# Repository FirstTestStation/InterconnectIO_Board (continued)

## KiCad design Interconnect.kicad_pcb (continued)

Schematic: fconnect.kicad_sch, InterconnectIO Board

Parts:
J1, J2: 9001-11961C00A; 900111961C00A; Manufacturer_Part_Number 9001-11961C00A
J3, J4: 7760; Manufacturer_Part_Number 7760; Mouser_Part_Number 534-7760
NT48: JA1; NetTie-2_Front1.0mm
NT49: JB18; NetTie-2_Front1.0mm
NT50: K10_H; NetTie-2_Front1.0mm
NT51: K31_L; NetTie-2_Front1.0mm
NT52: JA2; NetTie-2_Front1.0mm
NT53: JB19; NetTie-2_Front1.0mm
NT54: K10_L; NetTie-2_Front1.0mm
NT55: K34_H; NetTie-2_Front1.0mm
NT56: JA3; NetTie-2_Front1.0mm
NT57: JB20; NetTie-2_Front1.0mm
NT58: K13_H; NetTie-2_Front1.0mm
NT59: K34_L; NetTie-2_Front1.0mm
NT60: JA4; NetTie-2_Front1.0mm
NT61: JB21; NetTie-2_Front1.0mm
NT62: K13_L; NetTie-2_Front1.0mm
NT63: K37_H; NetTie-2_Front1.0mm
NT64: JA5; NetTie-2_Front1.0mm
NT65: JB22; NetTie-2_Front1.0mm
NT66: K16_H; NetTie-2_Front1.0mm
NT67: K37_L; NetTie-2_Front1.0mm
NT68: JA6; NetTie-2_Front1.0mm
NT69: JB23; NetTie-2_Front1.0mm
NT70: K16_L; NetTie-2_Front1.0mm
NT71: JA7; NetTie-2_Front1.0mm
NT72: JB24; NetTie-2_Front1.0mm
NT73: OCH1_H; NetTie-2_Front1.0mm
NT74: JA8; NetTie-2_Front1.0mm
NT75: JB25; NetTie-2_Front1.0mm
NT76: OCH1_L; NetTie-2_Front1.0mm
NT77: K41_H; NetTie-2_Front1.0mm
NT78: JA9; NetTie-2_Front1.0mm
NT79: JB26; NetTie-2_Front1.0mm
NT80: K20_H; NetTie-2_Front1.0mm
NT81: K41_L; NetTie-2_Front1.0mm
NT82: JA10; NetTie-2_Front1.0mm
NT83: JB27; NetTie-2_Front1.0mm
NT84: K20_L; NetTie-2_Front1.0mm
NT85: K44_H; NetTie-2_Front1.0mm
NT86: JA11; NetTie-2_Front1.0mm
NT87: JB28; NetTie-2_Front1.0mm
NT88: K23_H; NetTie-2_Front1.0mm
NT89: K44_L; NetTie-2_Front1.0mm
NT90: JA12; NetTie-2_Front1.0mm
NT91: JB29; NetTie-2_Front1.0mm
NT92: K23_L; NetTie-2_Front1.0mm
NT93: K47_H; NetTie-2_Front1.0mm
NT94: JA13; NetTie-2_Front1.0mm
NT95: JB30; NetTie-2_Front1.0mm
NT96: K26_H; NetTie-2_Front1.0mm
NT97: K47_L; NetTie-2_Front1.0mm
NT98: JA14; NetTie-2_Front1.0mm
NT99: JB31; NetTie-2_Front1.0mm
NT100: K26_L; NetTie-2_Front1.0mm
NT101: VM_I; NetTie-2_Front1.0mm
NT102: JA15; NetTie-2_Front1.0mm
NT103: JB32; NetTie-2_Front1.0mm
NT104: OCH2_H; NetTie-2_Front1.0mm
NT105: VM_T; NetTie-2_Front1.0mm
NT106: JA16; NetTie-2_Front1.0mm
NT107: JC1; NetTie-2_Front1.0mm
NT108: OCH2_L; NetTie-2_Front1.0mm
NT109: K12_H; NetTie-2_Front1.0mm
NT110: JA17; NetTie-2_Front1.0mm
NT111: JC2; NetTie-2_Front1.0mm
NT112: K30_H; NetTie-2_Front1.0mm
NT113: K12_L; NetTie-2_Front1.0mm
NT114: JA18; NetTie-2_Front1.0mm
NT115: JC3; NetTie-2_Front1.0mm
NT116: K30_L; NetTie-2_Front1.0mm
NT117: K15_H; NetTie-2_Front1.0mm
NT118: JA19; NetTie-2_Front1.0mm
NT119: JC4; NetTie-2_Front1.0mm
NT120: K33_H; NetTie-2_Front1.0mm
NT121: K15_L; NetTie-2_Front1.0mm
NT122: JA20; NetTie-2_Front1.0mm
NT123: JC5; NetTie-2_Front1.0mm
NT124: K33_L; NetTie-2_Front1.0mm
NT125: K1_CH; NetTie-2_Front1.0mm
NT126: JA21; NetTie-2_Front1.0mm
NT127: JC6; NetTie-2_Front1.0mm
NT128: K36_H; NetTie-2_Front1.0mm
NT129: K1_CL; NetTie-2_Front1.0mm
NT130: JA22; NetTie-2_Front1.0mm
NT131: JC7; NetTie-2_Front1.0mm
NT132: K36_L; NetTie-2_Front1.0mm
NT133: JA23; NetTie-2_Front1.0mm
NT134: JC8; NetTie-2_Front1.0mm
NT135: SG1_H; NetTie-2_Front1.0mm
NT136: K_OC1; NetTie-2_Front1.0mm
NT137: JA24; NetTie-2_Front1.0mm
NT138: JC9; NetTie-2_Front1.0mm
NT139: SG1_L; NetTie-2_Front1.0mm
NT140: K22_H; NetTie-2_Front1.0mm
NT141: JA25; NetTie-2_Front1.0mm
NT142: JC10; NetTie-2_Front1.0mm
NT143: K40_H; NetTie-2_Front1.0mm
NT144: K22_L; NetTie-2_Front1.0mm
NT145: JA26; NetTie-2_Front1.0mm
NT146: JC11; NetTie-2_Front1.0mm
NT147: K40_L; NetTie-2_Front1.0mm
NT148: K25_H; NetTie-2_Front1.0mm
NT149: JA27; NetTie-2_Front1.0mm
NT150: JC12; NetTie-2_Front1.0mm
NT151: K43_H; NetTie-2_Front1.0mm
NT152: K25_L; NetTie-2_Front1.0mm
NT153: RXH; NetTie-2_Front1.0mm
NT154: JC13; NetTie-2_Front1.0mm
NT155: K43_L; NetTie-2_Front1.0mm
NT156: K2_CH; NetTie-2_Front1.0mm
NT157: RXL; NetTie-2_Front1.0mm
NT158: JC14; NetTie-2_Front1.0mm
NT159: K46_H; NetTie-2_Front1.0mm
NT160: K2_CL; NetTie-2_Front1.0mm
NT161: JA30; NetTie-2_Front1.0mm
NT162: JC15; NetTie-2_Front1.0mm
NT163: K46_L; NetTie-2_Front1.0mm
NT164: TXH; NetTie-2_Front1.0mm
NT165: JC16; NetTie-2_Front1.0mm
NT166: VM_H; NetTie-2_Front1.0mm
NT167: K_OC2; NetTie-2_Front1.0mm
NT168: TXL; NetTie-2_Front1.0mm
NT169: JC17; NetTie-2_Front1.0mm
NT170: VM_L; NetTie-2_Front1.0mm
NT171: K32_H; NetTie-2_Front1.0mm
NT172: JB1; NetTie-2_Front1.0mm
NT173: JC18; NetTie-2_Front1.0mm
NT174: K11_H; NetTie-2_Front1.0mm
NT175: K32_L; NetTie-2_Front1.0mm
NT176: JB2; NetTie-2_Front1.0mm
NT177: JC19; NetTie-2_Front1.0mm
NT178: K11_L; NetTie-2_Front1.0mm
NT179: K35_H; NetTie-2_Front1.0mm
NT180: JB3; NetTie-2_Front1.0mm
NT181: JC20; NetTie-2_Front1.0mm
NT182: K14_H; NetTie-2_Front1.0mm
NT183: K35_L; NetTie-2_Front1.0mm
NT184: JB4; NetTie-2_Front1.0mm
NT185: JC21; NetTie-2_Front1.0mm
NT186: K14_L; NetTie-2_Front1.0mm
NT187: K3_CH; NetTie-2_Front1.0mm
NT188: JB5; NetTie-2_Front1.0mm
NT189: JC22; NetTie-2_Front1.0mm
NT190: K17_H; NetTie-2_Front1.0mm
NT191: K3_CL; NetTie-2_Front1.0mm
NT192: JB6; NetTie-2_Front1.0mm
NT193: JC23; NetTie-2_Front1.0mm
NT194: K17_L; NetTie-2_Front1.0mm
NT195: JB7; NetTie-2_Front1.0mm
NT196: JC24; NetTie-2_Front1.0mm
NT197: KI1_H; NetTie-2_Front1.0mm
NT198: K_OC3; NetTie-2_Front1.0mm
NT199: JB8; NetTie-2_Front1.0mm
NT200: JC25; NetTie-2_Front1.0mm
NT201: KI1_L; NetTie-2_Front1.0mm
NT202: K42_H; NetTie-2_Front1.0mm
NT203: JB9; NetTie-2_Front1.0mm
NT204: JC26; NetTie-2_Front1.0mm
NT205: K21_H; NetTie-2_Front1.0mm
NT206: K42_L; NetTie-2_Front1.0mm
NT207: JB10; NetTie-2_Front1.0mm
NT208: JC27; NetTie-2_Front1.0mm
NT209: K21_L; NetTie-2_Front1.0mm
NT210: K45_H; NetTie-2_Front1.0mm
NT211: JB11; NetTie-2_Front1.0mm
NT212: JC28; NetTie-2_Front1.0mm
NT213: K24_H; NetTie-2_Front1.0mm
NT214: K45_L; NetTie-2_Front1.0mm
NT215: JB12; NetTie-2_Front1.0mm
NT216: JC29; NetTie-2_Front1.0mm
NT217: K24_L; NetTie-2_Front1.0mm
NT218: K4_CH; NetTie-2_Front1.0mm
NT219: JB13; NetTie-2_Front1.0mm
NT220: JC30; NetTie-2_Front1.0mm
NT221: K27_H; NetTie-2_Front1.0mm
NT222: K4_CL; NetTie-2_Front1.0mm
NT223: JB14; NetTie-2_Front1.0mm
NT224: JC31; NetTie-2_Front1.0mm
NT225: K27_L; NetTie-2_Front1.0mm
NT226: VMS_H; NetTie-2_Front1.0mm
NT227: JB15; NetTie-2_Front1.0mm
NT228: JC32; NetTie-2_Front1.0mm
NT229: VMS_L; NetTie-2_Front1.0mm
NT230: JB16; NetTie-2_Front1.0mm
NT231: JB17; NetTie-2_Front1.0mm
NT232: K31_H; NetTie-2_Front1.0mm
TP17: J_A5; Pin_D0.9mm_L10.0mm_W2.4mm_FlatFork
TP18: J_A6; Pin_D0.9mm_L10.0mm_W2.4mm_FlatFork
TP19: K_B23; Pin_D0.9mm_L10.0mm_W2.4mm_FlatFork
TP20: K_B24; Pin_D0.9mm_L10.0mm_W2.4mm_FlatFork
TP21: J_A10; Pin_D0.9mm_L10.0mm_W2.4mm_FlatFork
TP22: J_A23; Pin_D0.9mm_L10.0mm_W2.4mm_FlatFork
TP23: J_B6; Pin_D0.9mm_L10.0mm_W2.4mm_FlatFork
TP24: K_B15; Pin_D0.9mm_L10.0mm_W2.4mm_FlatFork
TP25: K_B16; Pin_D0.9mm_L10.0mm_W2.4mm_FlatFork

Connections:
1W_DATA: NT177.1; also elsewhere on the board
AWG_H: NT135.2; also elsewhere on the board
AWG_L: NT139.2; also elsewhere on the board
B1_COM_H: NT125.1; also elsewhere on the board
B1_COM_L: NT129.1; also elsewhere on the board
B2_COM_H: NT156.1; also elsewhere on the board
B2_COM_L: NT160.1; also elsewhere on the board
B3_COM_H: NT187.1; also elsewhere on the board
B3_COM_L: NT191.1; also elsewhere on the board
B4_COM_H: NT218.1; also elsewhere on the board
B4_COM_L: NT222.1; also elsewhere on the board
B10_H: NT50.2; also elsewhere on the board
B10_L: NT54.2; also elsewhere on the board
B11_H: NT174.2; also elsewhere on the board
B11_L: NT178.2; also elsewhere on the board
B12_H: NT109.2; also elsewhere on the board
B12_L: NT113.2; also elsewhere on the board
B13_H: NT58.2; also elsewhere on the board
B13_L: NT62.2; also elsewhere on the board
B14_H: NT182.2; also elsewhere on the board
B14_L: NT186.2; also elsewhere on the board
B15_H: NT117.2; also elsewhere on the board
B15_L: NT121.2; also elsewhere on the board
B16_H: NT66.2; also elsewhere on the board
B16_L: NT70.2; also elsewhere on the board
B17_H: NT190.2; also elsewhere on the board
B17_L: NT194.2; also elsewhere on the board
B20_H: NT80.2; also elsewhere on the board
B20_L: NT84.2; also elsewhere on the board
B21_H: NT205.2; also elsewhere on the board
B21_L: NT209.2; also elsewhere on the board
B22_H: NT140.2; also elsewhere on the board
B22_L: NT144.2; also elsewhere on the board
B23_H: NT88.2; also elsewhere on the board
B23_L: NT92.2; also elsewhere on the board
B24_H: NT213.2; also elsewhere on the board
B24_L: NT217.2; also elsewhere on the board
B25_H: NT148.2; also elsewhere on the board
B25_L: NT152.2; also elsewhere on the board
B26_H: NT96.2; also elsewhere on the board
B26_L: NT100.2; also elsewhere on the board
B27_H: NT221.2; also elsewhere on the board
B27_L: NT225.2; also elsewhere on the board
B30_H: NT112.2; also elsewhere on the board
B30_L: NT116.2; also elsewhere on the board
B31_H: NT232.2; also elsewhere on the board
B31_L: NT51.2; also elsewhere on the board
B32_H: NT171.2; also elsewhere on the board
B32_L: NT175.2; also elsewhere on the board
B33_H: NT120.2; also elsewhere on the board
B33_L: NT124.2; also elsewhere on the board
B34_H: NT55.2; also elsewhere on the board
B34_L: NT59.2; also elsewhere on the board
B35_H: NT179.2; also elsewhere on the board
B35_L: NT183.2; also elsewhere on the board
B36_H: NT128.2; also elsewhere on the board
B36_L: NT132.2; also elsewhere on the board
B37_H: NT63.2; also elsewhere on the board
B37_L: NT67.2; also elsewhere on the board
B40_H: NT143.2; also elsewhere on the board
B40_L: NT147.2; also elsewhere on the board
B41_H: NT77.2; also elsewhere on the board
B41_L: NT81.2; also elsewhere on the board
B42_H: NT202.2; also elsewhere on the board
B42_L: NT206.2; also elsewhere on the board
B43_H: NT151.2; also elsewhere on the board
B43_L: NT155.2; also elsewhere on the board
B44_H: NT85.2; also elsewhere on the board
B44_L: NT89.2; also elsewhere on the board
B45_H: NT210.2; also elsewhere on the board
B45_L: NT214.2; also elsewhere on the board
B46_H: NT159.2; also elsewhere on the board
B46_L: NT163.2; also elsewhere on the board
B47_H: NT93.2; also elsewhere on the board
B47_L: NT97.2; also elsewhere on the board
CMOD_1: NT107.1; also elsewhere on the board
CMOD_2: NT111.1; also elsewhere on the board
CMOD_3: NT115.1; also elsewhere on the board
CMOD_4: NT119.1; also elsewhere on the board
CUR_SENS_H: NT185.1; also elsewhere on the board
CUR_SENS_L: NT189.1; also elsewhere on the board
DAC_VOUT: NT184.1; also elsewhere on the board
DIG_PWR_IN: NT208.1; also elsewhere on the board
DVM_H: NT166.2; also elsewhere on the board
DVM_I: NT101.2; also elsewhere on the board
DVM_L: NT170.2; also elsewhere on the board
DVM_SENSE_H: NT226.2; also elsewhere on the board
DVM_SENSE_L: NT229.2; also elsewhere on the board
DVM_TRIG: NT105.2; also elsewhere on the board
ETH_RX+: NT153.1; also elsewhere on the board
ETH_RX-: NT157.1; also elsewhere on the board
ETH_TX+: NT164.1; also elsewhere on the board
ETH_TX-: NT168.1; also elsewhere on the board
Earth: J1.MH1, J1.MH2, J2.MH1, J2.MH2, J3.1, J3.2, J3.3, J3.4, J4.1, J4.2, J4.3, J4.4; also elsewhere on the board
GND: J2.C7, J2.C15, J2.C23, NT98.1, NT161.1, NT180.1, NT181.1, NT188.1; also elsewhere on the board
I2C_SCL: NT94.1; also elsewhere on the board
I2C_SDA: NT90.1; also elsewhere on the board
INST_H: NT197.1; also elsewhere on the board
INST_L: NT201.1; also elsewhere on the board
JTAG_IGND: NT122.1; also elsewhere on the board
JTAG_OGND: NT110.1; also elsewhere on the board
JTAG_TCK: NT126.1; also elsewhere on the board
JTAG_TDI: NT118.1; also elsewhere on the board
JTAG_TDO: NT106.1; also elsewhere on the board
JTAG_TGND: NT130.1; also elsewhere on the board
JTAG_TMS: NT114.1; also elsewhere on the board
JTAG_TRST: NT102.1; also elsewhere on the board
K1_LP_C1: NT195.1; also elsewhere on the board
K1_LP_C2: NT131.1; also elsewhere on the board
K1_LP_NC1: NT203.1; also elsewhere on the board
K1_LP_NC2: NT138.1; also elsewhere on the board
K1_LP_NO1: NT199.1; also elsewhere on the board
K1_LP_NO2: NT134.1; also elsewhere on the board
K2_LP_C1: NT207.1; also elsewhere on the board
K2_LP_C2: NT142.1; also elsewhere on the board
K2_LP_NC1: NT215.1; also elsewhere on the board
K2_LP_NC2: NT150.1; also elsewhere on the board
K2_LP_NO1: NT211.1; also elsewhere on the board
K2_LP_NO2: NT146.1; also elsewhere on the board
K3_HP_C1: NT154.1; also elsewhere on the board
K3_HP_C2: NT158.1; also elsewhere on the board
K3_HP_NO1: NT162.1; also elsewhere on the board
K3_HP_NO2: NT165.1; also elsewhere on the board
unnamed: J1.A1, NT48.2
unnamed: J1.A2, NT52.2
unnamed: J1.A3, NT56.2
unnamed: J1.A4, NT60.2
unnamed: J1.A5, NT64.2
unnamed: J1.A6, NT68.2
unnamed: J1.A7, NT71.2
unnamed: J1.A8, NT74.2
unnamed: J1.A9, NT78.2
unnamed: J1.A10, NT82.2
unnamed: J1.A11, NT86.2
unnamed: J1.A12, NT90.2
unnamed: J1.A13, NT94.2
unnamed: J1.A14, NT98.2
unnamed: J1.A15, NT102.2
unnamed: J1.A16, NT106.2
unnamed: J1.A17, NT110.2
unnamed: J1.A18, NT114.2
unnamed: J1.A19, NT118.2
unnamed: J1.A20, NT122.2
unnamed: J1.A21, NT126.2
unnamed: J1.A22, NT130.2
unnamed: J1.A23, NT133.2
unnamed: J1.A24, NT137.2
unnamed: J1.A25, NT141.2
unnamed: J1.A26, NT145.2
unnamed: J1.A27, NT149.2
unnamed: J1.A28, NT153.2
unnamed: J1.A29, NT157.2
unnamed: J1.A30, NT161.2
unnamed: J1.A31, NT164.2
unnamed: J1.A32, NT168.2
unnamed: J1.B1, NT172.2
unnamed: J1.B2, NT176.2
unnamed: J1.B3, NT180.2
unnamed: J1.B4, NT184.2
unnamed: J1.B5, NT188.2
unnamed: J1.B6, NT192.2
unnamed: J1.B7, NT195.2
unnamed: J1.B8, NT199.2
unnamed: J1.B9, NT203.2
unnamed: J1.B10, NT207.2
unnamed: J1.B11, NT211.2
unnamed: J1.B12, NT215.2
unnamed: J1.B13, NT219.2
unnamed: J1.B14, NT223.2
unnamed: J1.B15, NT227.2
unnamed: J1.B16, NT230.2
unnamed: J1.B17, NT231.2
unnamed: J1.B18, NT49.2
unnamed: J1.B19, NT53.2
unnamed: J1.B20, NT57.2
unnamed: J1.B21, NT61.2
unnamed: J1.B22, NT65.2
unnamed: J1.B23, NT69.2
unnamed: J1.B24, NT72.2
unnamed: J1.B25, NT75.2
unnamed: J1.B26, NT79.2
unnamed: J1.B27, NT83.2
unnamed: J1.B28, NT87.2
unnamed: J1.B29, NT91.2
unnamed: J1.B30, NT95.2
unnamed: J1.B31, NT99.2
unnamed: J1.B32, NT103.2
unnamed: J1.C1, NT107.2
unnamed: J1.C2, NT111.2
unnamed: J1.C3, NT115.2
unnamed: J1.C4, NT119.2
unnamed: J1.C5, NT123.2
unnamed: J1.C6, NT127.2
unnamed: J1.C7, NT131.2
unnamed: J1.C8, NT134.2
unnamed: J1.C9, NT138.2
unnamed: J1.C10, NT142.2
unnamed: J1.C11, NT146.2
unnamed: J1.C12, NT150.2
unnamed: J1.C13, NT154.2
unnamed: J1.C14, NT158.2
unnamed: J1.C15, NT162.2
unnamed: J1.C16, NT165.2
unnamed: J1.C17, NT169.2
unnamed: J1.C18, NT173.2
unnamed: J1.C19, NT177.2
unnamed: J1.C20, NT181.2
unnamed: J1.C21, NT185.2
unnamed: J1.C22, NT189.2
unnamed: J1.C23, NT193.2
unnamed: J1.C24, NT196.2
unnamed: J1.C25, NT200.2
unnamed: J1.C26, NT204.2
unnamed: J1.C27, NT208.2
unnamed: J1.C28, NT212.2
unnamed: J1.C29, NT216.2
unnamed: J1.C30, NT220.2
unnamed: J1.C31, NT224.2
unnamed: J1.C32, NT228.2
unnamed: J2.A1, NT50.1
unnamed: J2.A2, NT54.1
unnamed: J2.A3, NT58.1
unnamed: J2.A4, NT62.1
unnamed: J2.A5, NT66.1
unnamed: J2.A6, NT70.1
unnamed: J2.A7, NT73.1
unnamed: J2.A8, NT76.1
unnamed: J2.A9, NT80.1
unnamed: J2.A10, NT84.1
unnamed: J2.A11, NT88.1
unnamed: J2.A12, NT92.1
unnamed: J2.A13, NT96.1
unnamed: J2.A14, NT100.1
unnamed: J2.A15, NT104.2
unnamed: J2.A16, NT108.2
unnamed: J2.A17, NT112.1
unnamed: J2.A18, NT116.1
unnamed: J2.A19, NT120.1
unnamed: J2.A20, NT124.1
unnamed: J2.A21, NT128.1
unnamed: J2.A22, NT132.1
unnamed: J2.A23, NT135.1
unnamed: J2.A24, NT139.1
unnamed: J2.A25, NT143.1
unnamed: J2.A26, NT147.1
unnamed: J2.A27, NT151.1
unnamed: J2.A28, NT155.1
unnamed: J2.A29, NT159.1
unnamed: J2.A30, NT163.1
unnamed: J2.A31, NT166.1
unnamed: J2.A32, NT170.1
unnamed: J2.B1, NT174.1
unnamed: J2.B2, NT178.1
unnamed: J2.B3, NT182.1
unnamed: J2.B4, NT186.1
unnamed: J2.B5, NT190.1
unnamed: J2.B6, NT194.1
unnamed: J2.B7, NT197.2
unnamed: J2.B8, NT201.2
unnamed: J2.B9, NT205.1
unnamed: J2.B10, NT209.1
unnamed: J2.B11, NT213.1
unnamed: J2.B12, NT217.1
unnamed: J2.B13, NT221.1
unnamed: J2.B14, NT225.1
unnamed: J2.B15, TP24.1
unnamed: J2.B16, TP25.1
unnamed: J2.B17, NT232.1
unnamed: J2.B18, NT51.1
unnamed: J2.B19, NT55.1
unnamed: J2.B20, NT59.1
unnamed: J2.B21, NT63.1
unnamed: J2.B22, NT67.1
unnamed: J2.B23, TP19.1
unnamed: J2.B24, TP20.1
unnamed: J2.B25, NT77.1
unnamed: J2.B26, NT81.1
unnamed: J2.B27, NT85.1
unnamed: J2.B28, NT89.1
unnamed: J2.B29, NT93.1
unnamed: J2.B30, NT97.1
unnamed: J2.B31, NT101.1
unnamed: J2.B32, NT105.1
unnamed: J2.C1, NT109.1
unnamed: J2.C2, NT113.1
unnamed: J2.C3, NT117.1
unnamed: J2.C4, NT121.1
unnamed: J2.C5, NT125.2
unnamed: J2.C6, NT129.2
unnamed: J2.C8, NT136.2
unnamed: J2.C9, NT140.1
unnamed: J2.C10, NT144.1
unnamed: J2.C11, NT148.1
unnamed: J2.C12, NT152.1
unnamed: J2.C13, NT156.2
unnamed: J2.C14, NT160.2
unnamed: J2.C16, NT167.2
unnamed: J2.C17, NT171.1
unnamed: J2.C18, NT175.1
unnamed: J2.C19, NT179.1
unnamed: J2.C20, NT183.1
unnamed: J2.C21, NT187.2
unnamed: J2.C22, NT191.2
unnamed: J2.C24, NT198.2
unnamed: J2.C25, NT202.1
unnamed: J2.C26, NT206.1
unnamed: J2.C27, NT210.1
unnamed: J2.C28, NT214.1
unnamed: J2.C29, NT218.2
unnamed: J2.C30, NT222.2
unnamed: J2.C31, NT226.1
unnamed: J2.C32, NT229.1
unnamed: NT64.1, TP17.1
unnamed: NT68.1, TP18.1
unnamed: NT86.1, TP21.1
unnamed: NT133.1, TP22.1
unnamed: NT192.1, TP23.1
OC1_OUT: NT136.1; also elsewhere on the board
OC2_OUT: NT167.1; also elsewhere on the board
OC3_OUT: NT198.1; also elsewhere on the board
PCTRL: NT99.1; also elsewhere on the board
PERR_LED: NT60.1; also elsewhere on the board
PFLAG: NT103.1; also elsewhere on the board
PM2_IO8: NT48.1
PM2_IO9: NT52.1
PM2_IO28: NT56.1
PR0_0: NT227.1; also elsewhere on the board
PR0_1: NT230.1; also elsewhere on the board
PR0_2: NT231.1; also elsewhere on the board
PR0_3: NT49.1; also elsewhere on the board
PR0_4: NT53.1; also elsewhere on the board
PR0_5: NT57.1; also elsewhere on the board
PR0_6: NT61.1; also elsewhere on the board
PR0_7: NT65.1; also elsewhere on the board
PR1_0: NT69.1; also elsewhere on the board
PR1_1: NT72.1; also elsewhere on the board
PR1_2: NT75.1; also elsewhere on the board
PR1_3: NT79.1; also elsewhere on the board
PR1_4: NT83.1; also elsewhere on the board
PR1_5: NT87.1; also elsewhere on the board
PR1_6: NT91.1; also elsewhere on the board
PR1_7: NT95.1; also elsewhere on the board
PR_ADC0: NT172.1; also elsewhere on the board
PR_ADC1: NT176.1; also elsewhere on the board
PS1_IO8: NT219.1; also elsewhere on the board
PS1_IO9: NT223.1; also elsewhere on the board
PS1_OUT_HI1: NT193.1; also elsewhere on the board
PS1_OUT_HI2: NT196.1; also elsewhere on the board
PS1_OUT_LO1: NT200.1; also elsewhere on the board
PS1_OUT_LO2: NT204.1; also elsewhere on the board
PWR_5V: NT212.1; also elsewhere on the board
PWR_RES_H: NT123.1; also elsewhere on the board
PWR_RES_L: NT127.1; also elsewhere on the board
SCOPE_CH1_H: NT73.2; also elsewhere on the board
SCOPE_CH1_L: NT76.2; also elsewhere on the board
SCOPE_CH2_H: NT104.1; also elsewhere on the board
SCOPE_CH2_L: NT108.1; also elsewhere on the board
SERIAL_CTS: NT228.1; also elsewhere on the board
SERIAL_RTS: NT224.1; also elsewhere on the board
SERIAL_RX: NT220.1; also elsewhere on the board
SERIAL_TX: NT216.1; also elsewhere on the board
SSR1_NEG: NT173.1; also elsewhere on the board
SSR1_POS: NT169.1; also elsewhere on the board
USB_D+: NT141.1; also elsewhere on the board
USB_D-: NT145.1; also elsewhere on the board
USB_GND: NT149.1; also elsewhere on the board
USB_VBUS: NT137.1; also elsewhere on the board
USPI0_CLK: NT71.1; also elsewhere on the board
USPI0_CS: NT82.1; also elsewhere on the board
USPI0_RX: NT78.1; also elsewhere on the board
USPI0_TX: NT74.1; also elsewhere on the board

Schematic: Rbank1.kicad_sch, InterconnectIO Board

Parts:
C1: 10uF; CP_Radial_D4.0mm_P1.50mm
K1, K2, K3, K4, K5, K6, K7, K8, K9: TQ2-5; Relay_DPDT_FRT5
NT1: NT10_CH; NetTie-2_Front1.0mm
NT2: NT11_CH; NetTie-2_Front1.0mm
NT3: NT12_CH; NetTie-2_Front1.0mm
NT4: NT13_CH; NetTie-2_Front1.0mm
NT5: NT10_CL; NetTie-2_Front1.0mm
NT6: NT11_CL; NetTie-2_Front1.0mm
NT7: NT12_CL; NetTie-2_Front1.0mm
NT8: NT13_CL; NetTie-2_Front1.0mm
NT9: NT14_CH; NetTie-2_Front1.0mm
NT10: NT15_CH; NetTie-2_Front1.0mm
NT11: NT16_CH; NetTie-2_Front1.0mm
NT12: NT17_CH; NetTie-2_Front1.0mm
NT13: NT14_CL; NetTie-2_Front1.0mm
NT14: NT15_CL; NetTie-2_Front1.0mm
NT15: NT16_CL; NetTie-2_Front1.0mm
NT16: NT17_CL; NetTie-2_Front1.0mm
NT17, NT20: NT1S_RL; NetTie-2_Front1.0mm
NT18: NT1S_CH; NetTie-2_Front1.0mm
NT19: NT1S_NH; NetTie-2_Front1.0mm
NT21: NT1S_CL; NetTie-2_Front1.0mm
NT22: NT1S_L1; NetTie-2_Front1.0mm
TP1: NT10_HH; Pin_D0.9mm_L10.0mm_W2.4mm_FlatFork
TP2: NT11_HH; Pin_D0.9mm_L10.0mm_W2.4mm_FlatFork
TP3: NT12_HH; Pin_D0.9mm_L10.0mm_W2.4mm_FlatFork
TP4: NT13_HH; Pin_D0.9mm_L10.0mm_W2.4mm_FlatFork
TP5: NT10_LL; Pin_D0.9mm_L10.0mm_W2.4mm_FlatFork
TP6: NT11_LL; Pin_D0.9mm_L10.0mm_W2.4mm_FlatFork
TP7: NT12_LL; Pin_D0.9mm_L10.0mm_W2.4mm_FlatFork
TP8: NT13_LL; Pin_D0.9mm_L10.0mm_W2.4mm_FlatFork
TP9: NT14_HH; Pin_D0.9mm_L10.0mm_W2.4mm_FlatFork
TP10: NT15_HH; Pin_D0.9mm_L10.0mm_W2.4mm_FlatFork
TP11: NT16_HH; Pin_D0.9mm_L10.0mm_W2.4mm_FlatFork
TP12: NT17_HH; Pin_D0.9mm_L10.0mm_W2.4mm_FlatFork
TP13: NT14_LL; Pin_D0.9mm_L10.0mm_W2.4mm_FlatFork
TP14: NT15_LL; Pin_D0.9mm_L10.0mm_W2.4mm_FlatFork
TP15: NT16_LL; Pin_D0.9mm_L10.0mm_W2.4mm_FlatFork
TP16: NT17_LL; Pin_D0.9mm_L10.0mm_W2.4mm_FlatFork

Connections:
/Relay_Bank1/B10_CH: K1.8, NT1.2
/Relay_Bank1/B10_CL: K1.3, NT5.2
/Relay_Bank1/B11_CH: K2.8, NT2.2
/Relay_Bank1/B11_CL: K2.3, NT6.2
/Relay_Bank1/B12_CH: K3.8, NT3.2
/Relay_Bank1/B12_CL: K3.3, NT7.2
/Relay_Bank1/B13_CH: K4.8, NT4.2
/Relay_Bank1/B13_CL: K4.3, NT8.2
/Relay_Bank1/B14_CH: K5.8, NT9.2
/Relay_Bank1/B14_CL: K5.3, NT13.2
/Relay_Bank1/B15_CH: K6.8, NT10.2
/Relay_Bank1/B15_CL: K6.3, NT14.2
/Relay_Bank1/B16_CH: K7.8, NT11.2
/Relay_Bank1/B16_CL: K7.3, NT15.2
/Relay_Bank1/B17_CH: K8.8, NT12.2
/Relay_Bank1/B17_CL: K8.3, NT16.2
/Relay_Bank1/BANK1_BUS_H: NT5.1, NT6.1, NT7.1, NT8.1, NT13.1, NT14.1, NT15.1, NT16.1, NT19.2, NT20.2
/Relay_Bank1/BANK1_BUS_L: NT1.1, NT2.1, NT3.1, NT4.1, NT9.1, NT10.1, NT11.1, NT12.1, NT17.2, NT22.2
B1S_R: K9.10; also elsewhere on the board
B1_COM_H: NT18.1; also elsewhere on the board
B1_COM_L: NT21.1; also elsewhere on the board
B10_H: K1.7; also elsewhere on the board
B10_L: K1.4; also elsewhere on the board
B10_R: K1.10; also elsewhere on the board
B11_H: K2.7; also elsewhere on the board
B11_L: K2.4; also elsewhere on the board
B12_H: K3.7; also elsewhere on the board
B12_L: K3.4; also elsewhere on the board
B12_R: K3.10; also elsewhere on the board
B13_H: K4.7; also elsewhere on the board
B13_L: K4.4; also elsewhere on the board
B13_R: K4.10; also elsewhere on the board
B14_H: K5.7; also elsewhere on the board
B14_L: K5.4; also elsewhere on the board
B14_R: K5.10; also elsewhere on the board
B15_H: K6.7; also elsewhere on the board
B15_L: K6.4; also elsewhere on the board
B15_R: K6.10; also elsewhere on the board
B16_H: K7.7; also elsewhere on the board
B16_L: K7.4; also elsewhere on the board
B16_R: K7.10; also elsewhere on the board
B17_H: K8.7; also elsewhere on the board
B17_L: K8.4; also elsewhere on the board
B17_R: K8.10; also elsewhere on the board
GND: C1.2; also elsewhere on the board
unnamed: K1.2, TP5.1
unnamed: K1.9, TP1.1
unnamed: K2.2, TP6.1
unnamed: K2.9, TP2.1
unnamed: K3.2, TP7.1
unnamed: K3.9, TP3.1
unnamed: K4.2, TP8.1
unnamed: K4.9, TP4.1
unnamed: K5.2, TP13.1
unnamed: K5.9, TP9.1
unnamed: K6.2, TP14.1
unnamed: K6.9, TP10.1
unnamed: K7.2, TP15.1
unnamed: K7.9, TP11.1
unnamed: K8.2, TP16.1
unnamed: K8.9, TP12.1
unnamed: K9.2, NT22.1
unnamed: K9.3, NT21.2
unnamed: K9.4, NT20.1
unnamed: K9.7, NT17.1
unnamed: K9.8, NT18.2
unnamed: K9.9, NT19.1
PWR_5V: C1.1, K1.1, K2.1, K3.1, K4.1, K5.1, K6.1, K7.1, K8.1, K9.1; also elsewhere on the board

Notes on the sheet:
BANK1_CH3
BANK1_SE
BANK1_CH7
BANK1_CH5
BANK1_CH1
BANK1_CH4
BANK1_CH0
BANK1_CH2
BANK1_CH6

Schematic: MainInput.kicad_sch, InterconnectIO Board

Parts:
C9, C10, C11, C12: 100n; C_0201_0603Metric_Pad0.64x0.40mm_HandSolder
C13: 0.1uF; C_0603_1608Metric_Pad1.08x0.95mm_HandSolder
D34: 1N5339B; D_DO-201_P15.24mm_Horizontal
D35: LED; LED_D3.0mm
F1: MC000827
J27: PJ-082BH; CUI_PJ-082BH; PARTREV 1.0
J28: DB9_Female_RA; DSUB-9_Female_Horizontal_P2.77x2.84mm_EdgePinOffset4.94mm_H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
J29: Conn_01x04_Female; PinHeader_1x04_P2.54mm_Vertical
NT468: SER_12; NetTie-2_Front1.0mm
NT469: SER_11; NetTie-2_Front1.0mm
R68: 220; R_Axial_DIN0309_L9.0mm_D3.2mm_P12.70mm_Horizontal
S1: PB400EEQR1BLK; SW_PB400EEQR1BLK; PARTREV A
TP92: R2_OUT; Pin_D0.9mm_L10.0mm_W2.4mm_FlatFork
TP94: R1IN; Pin_D0.9mm_L10.0mm_W2.4mm_FlatFork
TP97: T2OUT; Pin_D0.9mm_L10.0mm_W2.4mm_FlatFork
TP98: T2IN; Pin_D0.9mm_L10.0mm_W2.4mm_FlatFork
U9: MAX3232; SOIC127P600X175-16N

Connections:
Earth: J27.S1 (SHIELD), J27.S2 (SHIELD), J27.S3 (SHIELD), J27.S4 (SHIELD), J28.0 (PAD); also elsewhere on the board
GND: C9.2, C10.2, C13.2, D34.2 (A), D35.2 (A), J28.5, J29.4, S1.4, U9.15 (GND); also elsewhere on the board
MSR_3V3: C13.1, J29.1, U9.16 (VCC); also elsewhere on the board
unnamed: C9.1, U9.6 (VS-)
unnamed: C10.1, U9.2 (VS+)
unnamed: C11.1, U9.5 (C2-)
unnamed: C11.2, U9.4 (C2+)
unnamed: C12.1, U9.3 (C1-)
unnamed: C12.2, U9.1 (C1+)
unnamed: D35.1 (K), R68.1
unnamed: F1.P$1, S1.2
unnamed: J27.1, S1.1
unnamed: J27.2, S1.3
unnamed: J28.2, U9.14 (T1OUT)
unnamed: J28.3, U9.8 (R2IN)
unnamed: NT468.1, U9.12 (R1OUT)
unnamed: NT469.1, U9.11 (T1IN)
unnamed: TP92.1, U9.9 (R2OUT)
unnamed: TP94.1, U9.13 (R1IN)
unnamed: TP97.1, U9.7 (T2OUT)
unnamed: TP98.1, U9.10 (T2IN)
PWR_5V: D34.1 (K), F1.P$2, R68.2; also elsewhere on the board
UART0_RX: J29.2, NT468.2; also elsewhere on the board
UART0_TX: J29.3, NT469.2; also elsewhere on the board

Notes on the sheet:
RS-232 TO TTL MODULE
FOOTPRINT WILL ACCEPT DIRECT IC SOLDERING OR PIGGY BACK MODULE MOUNTED ON TP
GREEN
5.6V

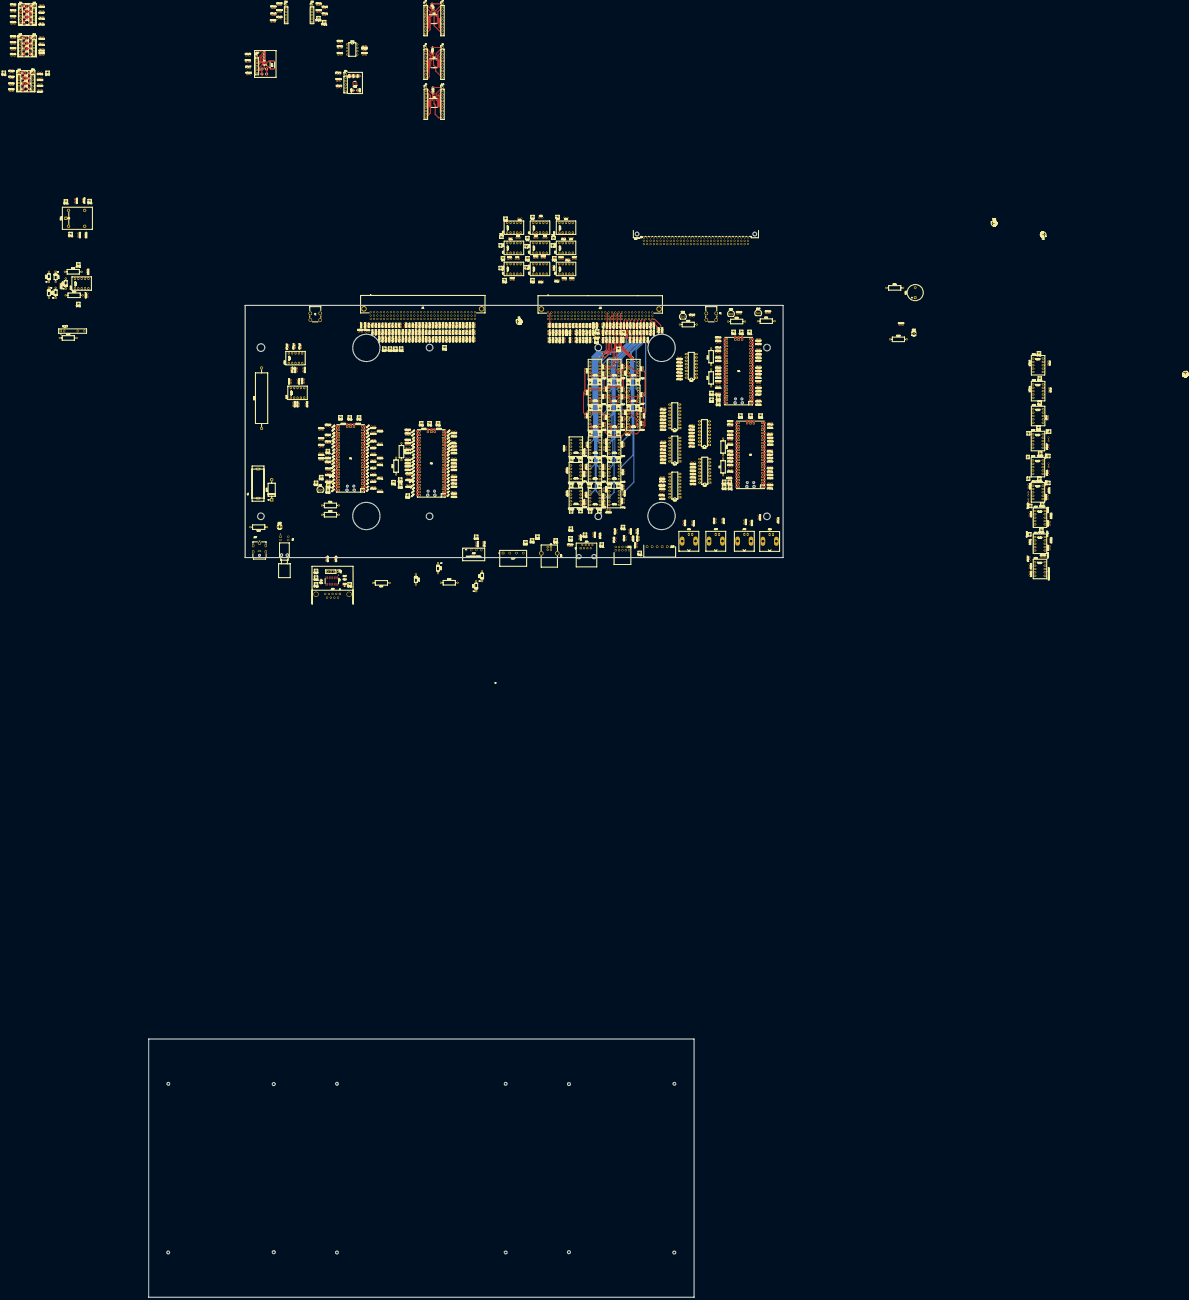
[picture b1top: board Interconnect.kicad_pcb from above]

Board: 4 copper layers, 845 parts (0 on the bottom side), 979 nets.

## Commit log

2023-01-09 First commit
    Initial schematics
2023-01-16 First try to fit electronic on PCB
2023-01-23 backup 1 bank done
2023-02-13 Relay bank wired
2023-02-17 half PCB completed
    FTS io controller PCB
2023-02-28 PCB Completed
    PCB completed but final verification not completed
2023-03-06 PCB completed
    All modification made
2023-03-06 PCB completed
2023-03-06 small update silkscreen
2023-03-07 Change custom connector
    Use 8 pins to replace 6 pins
2023-05-16 update
    Correction of small error
2023-08-09 V1.0 Commit
    PCB Design Completed
2023-08-09 Remove backup files
2023-08-09 Remove old files
2024-11-22 Doc moved to Libreoffice
2024-11-22 correct link on readme
2024-11-22 remove not necessary files
2024-12-02 Change TO-92 package to 2.54mm package
    Transistor and voltage reference using TO-92 Package will have the possibility to be mounted on in-line 3 pins socket of 2.54mm.
2025-01-08 add documentation partnumber and add BOM Pico controller socket and header
2025-01-08 update link on readme
2025-01-08 add partnumber to documentation
2025-02-06 Reverse COM_H and COM_L on relay Bank
2025-05-09 link correction on readme
